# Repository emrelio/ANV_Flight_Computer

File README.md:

Flight computer design for experimental model rocket flights.

I design this PCB for TVC of low power rockets.

Specs:

3-12V battery input,
  
Reverse battery protection,
  
3.3V and 5V switching regulators,
  
One main arm switch connector to cut all the power from the board,
  
Magnetic Switch connector for activation,
  
4, high current logic outputs,
  
All high current outputs have feedback for continuity detection,
  
4, 5v Servo outputs,
  
1,  LED and 1, active Buzzer connector,
  
1, RGB LED for notification,
  
ARM MCU,
  
Battery voltage and current sensors,
  
2, barometer from different brands for reliability,
  
9 DOF IMU,
  
4MB of memory for data logging,
  
Type-C connector for reading logged data,
  
433mHz LoRa for long-range wireless communication with U.FL connection,
  
Notification LED's for memory write and wireless communication,
  
Notification LED's for each high current outputs,
  
Screw terminal connector for power in-outs,
  
CAN-Bus connector for expansions in future,
  
M3 screw holes are connected to (BATT+, BATT-(GND), CAN-H, CAN-L).

Designed in KiCAD nightly.

Log:
  
Hall effect sensor out pin needs pull-up resistor, not pull-down. So It doesn't work.  
3.3V regulator acting abnormally. I might overheated it while soldering. Will try it on another board.  
IMU and Barometers are working.  
USB VCP is working.  
Current sensor is working.  
Mosfet feedback is working.  
Flash memory is working, logging algorithm is ready.  
Servo is working with integrated 5V regulator. Voltage might drop on load.  
  
To-Do :

Lora  
Can-Bus

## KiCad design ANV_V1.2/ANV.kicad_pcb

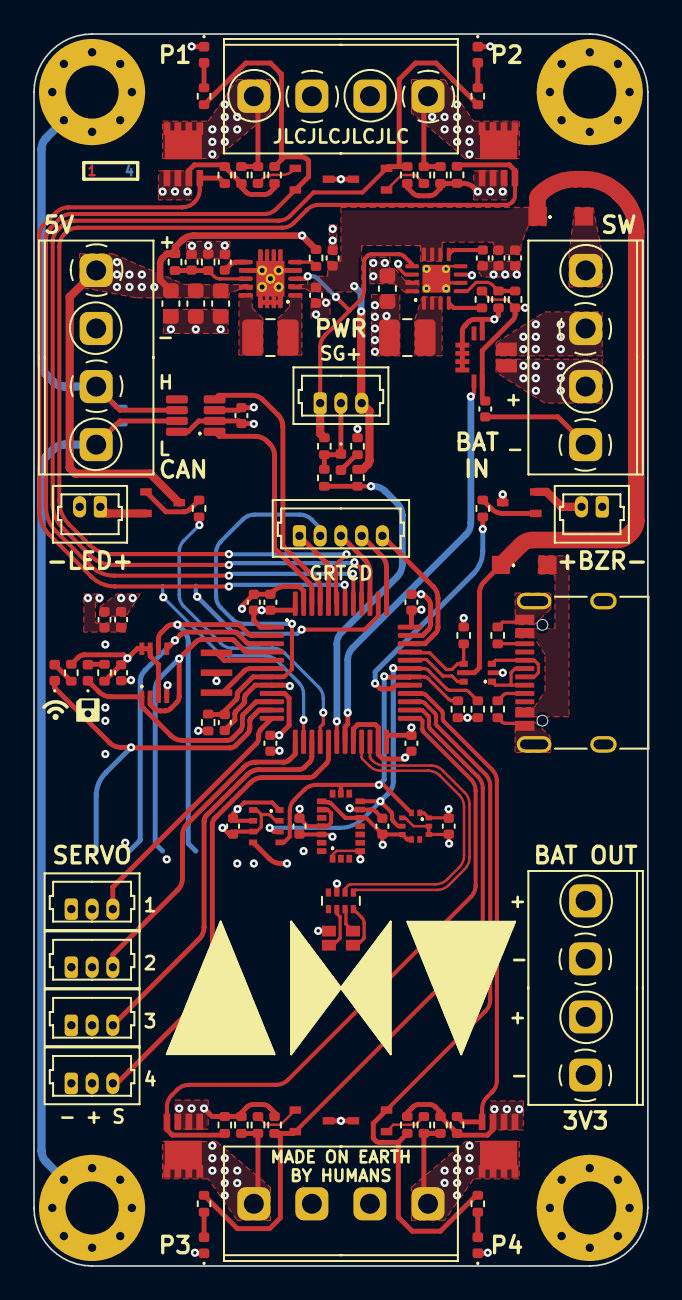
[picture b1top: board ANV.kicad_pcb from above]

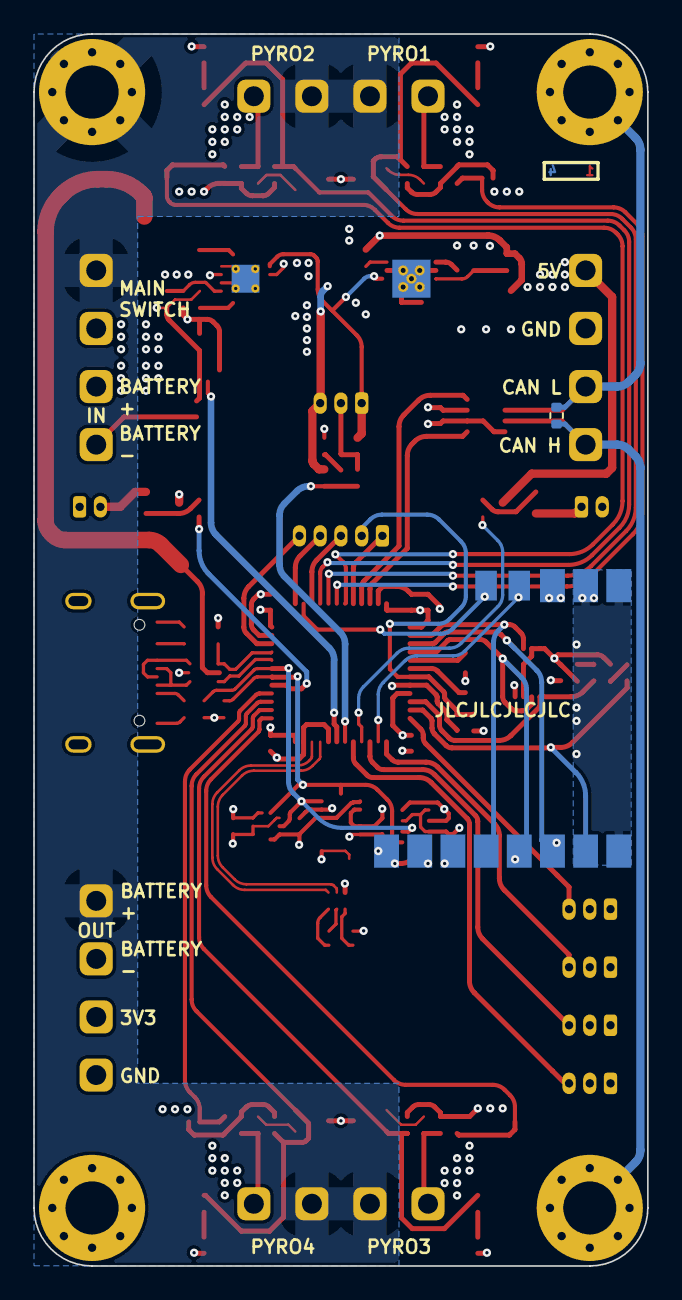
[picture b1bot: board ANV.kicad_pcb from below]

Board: 4 copper layers, 37.0 x 74.3 mm, 128 parts (2 on the bottom side), 83 nets.

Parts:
C1, C3, C7, C13, C14, C15, C16, C17, C18, C19, C20, C21, C23, C24, C25, C26, C27: 100nF; C_0402_1005Metric
C2, C4, C5: 10uF; C_0402_1005Metric
C6: 390pF; C_0402_1005Metric
C8: 10pF; C_0402_1005Metric
C9, C10, C11, C12: 22uF; C_0603_1608Metric
D1, D9: diode; D_SOD-123F
D2: flash; LED_0402_1005Metric
D3: pyro1; LED_0402_1005Metric
D4: pyro2; LED_0402_1005Metric
D5: pyro3; LED_0402_1005Metric
D6: pyro4; LED_0402_1005Metric
D7: 3v3; LED_0402_1005Metric
D8: RGB_Led; LED_LiteOn_LTST-C19HE1WT
D10: lora; LED_0402_1005Metric
H1: L; MountingHole_3.2mm_M3_Pad_Via
H2: H; MountingHole_3.2mm_M3_Pad_Via
H3: GND; MountingHole_3.2mm_M3_Pad_Via
H4: pwr; MountingHole_3.2mm_M3_Pad_Via
J1: programlama; Molex_PicoBlade_53047-0510_1x05_P1.25mm_Vertical
J2: Batt; 3.5mm_01x02_Screw_Terminal
J3: Sw; 3.5mm_01x02_Screw_Terminal
J4: USB_C_Receptacle_USB2.0; USB_C_Receptacle_XKB_U262-16XN-4BVC11
J5: switch/hallEffect; Molex_PicoBlade_53047-0310_1x03_P1.25mm_Vertical
J6: buzzer; Molex_PicoBlade_53047-0210_1x02_P1.25mm_Vertical
J7: 5v; 3.5mm_01x02_Screw_Terminal
J8: canbus; 3.5mm_01x02_Screw_Terminal
J9: led; Molex_PicoBlade_53047-0210_1x02_P1.25mm_Vertical
J10: pyro1; 3.5mm_01x02_Screw_Terminal
J11: pyro2; 3.5mm_01x02_Screw_Terminal
J12: pyro3; 3.5mm_01x02_Screw_Terminal
J13: pyro4; 3.5mm_01x02_Screw_Terminal
J14: servo1; Molex_PicoBlade_53047-0310_1x03_P1.25mm_Vertical
J15: servo2; Molex_PicoBlade_53047-0310_1x03_P1.25mm_Vertical
J16: batt; 3.5mm_01x02_Screw_Terminal
J17: 3v; 3.5mm_01x02_Screw_Terminal
J18: servo3; Molex_PicoBlade_53047-0310_1x03_P1.25mm_Vertical
J19: servo4; Molex_PicoBlade_53047-0310_1x03_P1.25mm_Vertical
L1: 1uH; L_1008_2520Metric
L2: 2.2uH; L_1008_2520Metric
LOGO1: anv; .A.N.V._Logo
LOGO2: rf; wifi
LOGO3: save; floppy
Q1, Q2, Q3, Q4: SE20N110; Vishay_PowerPAK_1212-8_Single
Q5, Q6, Q7, Q8, Q9, Q10: BC817W; SOT-323_SC-70
R1, R11: 100k; R_0402_1005Metric
R2: 30k; R_0402_1005Metric
R3, R4: 5k1; R_0402_1005Metric
R7, R12, R14, R15, R16, R17, R18, R19, R20, R21, R26, R27, R28, R29: 10k; R_0402_1005Metric
R8: 1k5; R_0402_1005Metric
R9, R39: 1m; R_0402_1005Metric
R10: 110k; R_0402_1005Metric
R13, R22, R23, R24, R25, R30, R31, R32, R33, R34, R35, R36, R45: 1k; R_0402_1005Metric
R37, R38: 4k7; R_0402_1005Metric
R40: 562k; R_0402_1005Metric
R41: 180k; R_0402_1005Metric
R44: 120r; R_0402_1005Metric
RN1: 1k; R_Array_Concave_4x0402
U1: ACS711xEXLT-15AB; Allegro_QFN-12-10-1EP_3x3mm_P0.5mm
U2: USBLC6-2P6; SOT-666
U3: TLV62130ARGTR; VQFN-16-1EP_3x3mm_P0.5mm_EP1.68x1.68mm_ThermalVias
U4: TPS63060; Texas_S-PWSON-N10_ThermalVias
U5: STM32F302C8Tx; LQFP-48_7x7mm_P0.5mm
U6: W25X40CLUXIG; DFN-8-1EP_3x2mm_P0.5mm_EP1.3x1.5mm
U7: LPS22HBTR; LPS22HB
U8: BMP280; Bosch_LGA-8_2x2.5mm_P0.65mm_ClockwisePinNumbering
U9: BMX055
U11: MAX3051; SOT-23-8
U12: Ai-Thinker-Ra-02; Ai-Thinker-Ra-01-LoRa
Y1: 8mHz; Resonator_SMD_muRata_CSTxExxV-3Pin_3.0x1.1mm

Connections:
+3V3: C1.1, C10.1, C14.2, C15.2, C16.2, C17.2, C18.2, C19.2, C20.1, C21.1, C23.2, C24.2, C25.2, C26.2, C27.2, D8.2 (VCC), J17.2, L2.2, Q5.3 (C), Q6.3 (C), Q9.3 (C), Q10.3 (C), R8.1, R11.1, R12.1, R13.1, R36.1, R37.1, R38.1, R40.1, R45.1, U1.10 (VCC), U3.7 (FSW), U3.14 (VOS), U5.1 (VBAT), U5.9 (VDDA), U5.24 (VDD), U5.36 (VDD), U5.48 (VDD), U6.3 (IO2), U6.7 (IO3), U6.8 (VCC), U7.1 (VDD_IO), U7.5 (SDO), U7.6 (CS), U7.10 (VDD), U8.2 (CSB), U8.6 (VDDIO), U8.8 (VDD), U9.3 (VDD), U9.7 (PS), U9.13 (VDDIO), U11.3 (VDD), U12.3 (VDD)
+5V: C9.1, C11.1, C12.1, J7.1, J14.2, J15.2, J18.2, J19.2, Q7.3 (C), Q8.3 (C), R9.1, R39.1, U4.9 (VOUT)
A0: D2.1 (K), U5.10 (PA0), U6.1 (~CS)
A1: D10.1 (K), U5.11 (PA1), U12.15 (~NSS)
A2: J14.3, U5.12 (PA2)
A3: J15.3, U5.13 (PA3)
A5: J18.3, U5.15 (PA5)
A6: R31.1, U5.16 (PA6)
A7: J19.3, U5.17 (PA7)
A8: R30.1, U5.29 (PA8)
A9: R37.2, U5.30 (PA9), U7.2 (SCL), U8.4 (SCK), U9.9 (SCX)
A10: R38.2, U5.31 (PA10), U7.4 (SDA), U8.3 (SDI), U9.11 (SDX)
A15: U5.38 (PA15), U12.5 (DIO0)
B0: R1.1, R2.2, U5.18 (PB0)
B1: U1.9 (VIOUT), U5.19 (PB1)
B3: J1.3, U5.39 (PB3)
B4: Q6.2 (E), R27.2, R33.1, U5.40 (PB4)
B5: Q5.2 (E), R26.2, R32.1, U5.41 (PB5)
B6: Q1.4 (G), R14.2, U5.42 (PB6)
B7: Q2.4 (G), R15.2, U5.43 (PB7)
B10: RN1.2 (R2.1), U5.21 (PB10)
B11: RN1.1 (R1.1), U5.22 (PB11)
B12: Q3.4 (G), R16.2, U5.25 (PB12)
B13: Q9.2 (E), R28.2, R34.1, U5.26 (PB13)
B14: Q10.2 (E), R29.2, R35.1, U5.27 (PB14)
B15: Q4.4 (G), R17.2, U5.28 (PB15)
Batt_+: C2.1, C3.1, C4.1, C5.1, D1.1 (K), D9.1 (K), J5.3, R1.2, U2.5 (VBUS), U3.10 (AVIN), U3.11 (PVIN), U3.12 (PVIN), U4.2 (VIN)
Batt_Pyro: D9.2 (A), H4.1, J3.2, J10.1, J11.2, J12.2, J13.1, J16.2
C13: U5.2 (PC13), U6.6 (CLK), U12.12 (SCK)
C14: U5.3 (PC14), U6.5 (DI(IO0)), U12.14 (MOSI)
C15: U5.4 (PC15), U6.2 (DO(IO1)), U12.13 (MISO)
GND: C1.2, C2.2, C3.2, C4.2, C5.2, C6.1, C7.2, C8.2, C9.2, C10.2, C11.2, C12.2, C13.1, C14.1, C15.1, C16.1, C17.1, C18.1, C19.1, C20.2, C21.2, C23.1, C24.1, C25.1, C26.1, C27.1, D3.1 (K), D4.1 (K), D5.1 (K), D6.1 (K), D7.1 (K), H3.1, J1.1, J2.1, J4.A1 (GND), J4.A12 (GND), J4.B1 (GND), J4.B12 (GND), J4.S1 (SHIELD), J5.2, J6.1, J7.2, J9.2, J14.1, J15.1, J16.1, J17.1, J18.1, J19.1, Q1.1 (S), Q1.2 (S), Q1.3 (S), Q2.1 (S), Q2.2 (S), Q2.3 (S), Q3.1 (S), Q3.2 (S), Q3.3 (S), Q4.1 (S), Q4.2 (S), Q4.3 (S), R2.1, R3.2, R4.2, R7.1, R10.2, R14.1, R15.1, R16.1, R17.1, R18.1, R19.1, R20.1, R21.1, R26.1, R27.1, R28.1, R29.1, R41.2, RN1.3 (R3.1), U1.3 (GND), U1.5 (NC), U1.6 (NC), U1.7 (NC), U1.8 (NC), U2.2 (GND), U3.6 (AGND), U3.8 (DEF), U3.15 (PGND), U3.16 (PGND), U3.17 (THERMAL_PAD), U4.4 (PS/SYNC), U4.7 (GND), U4.11 (PGND), U5.8 (VSSA), U5.20 (PB2), U5.23 (VSS), U5.35 (VSS), U5.44 (BOOT0), U5.47 (VSS), U6.4 (GND), U7.3 (-), U7.8 (GND), U7.9 (GND), U8.1 (GND), U8.5 (SDO), U8.7 (GND), U9.4 (GNDA), U9.6 (GNDIO), U9.12 (SDO2), U9.17 (SDO1), U9.20 (CSB3(magnet)), U11.2 (GND), U11.8 (RS), U12.1 (GND), U12.2 (GND), U12.9 (GND), U12.16 (GND), Y1.2
unnamed: C6.2, U3.9 (SS/TR)
unnamed: C7.1, U4.6 (VAUX)
unnamed: C8.1, R9.2, R10.1, U4.8 (FB)
unnamed: D1.2 (A), J4.A4 (VBUS), J4.A9 (VBUS), J4.B4 (VBUS), J4.B9 (VBUS)
unnamed: D2.2 (A), R13.2
unnamed: D3.2 (A), R32.2
unnamed: D4.2 (A), R33.2
unnamed: D5.2 (A), R34.2
unnamed: D6.2 (A), R35.2
unnamed: D7.2 (A), R36.2
unnamed: D8.1 (B), RN1.6 (R3.2)
unnamed: D8.3 (G), RN1.7 (R2.2)
unnamed: D8.4 (R), RN1.8 (R1.2)
unnamed: D10.2 (A), R45.2
unnamed: J2.2, U1.1 (IP+)
unnamed: J3.1, U1.2 (IP-)
unnamed: J4.A5 (CC1), R3.1
unnamed: J4.A6 (D+), J4.B6 (D+), U2.3 (I/O2)
unnamed: J4.A7 (D-), J4.B7 (D-), U2.1 (I/O1)
unnamed: J4.B5 (CC2), R4.1
unnamed: L1.1, U4.1 (L1)
unnamed: L1.2, U4.10 (L2)
unnamed: L2.1, U3.1 (SW), U3.2 (SW), U3.3 (SW)
unnamed: Q5.1 (B), R22.2
unnamed: Q6.1 (B), R23.2
unnamed: Q7.1 (B), R30.2
unnamed: Q8.1 (B), R31.2
unnamed: Q9.1 (B), R24.2
unnamed: Q10.1 (B), R25.2
unnamed: R11.2, U3.4 (PG)
unnamed: R39.2, U4.5 (PG)
unnamed: R40.2, R41.1, U3.5 (FB)
unnamed: U5.5 (PF0), Y1.1
unnamed: U5.6 (PF1), Y1.3
Reset: C13.2, J1.2, R12.2, U5.7 (NRST)
SWCLK: J1.4, U5.37 (PA14)
SWDIO: J1.5, U5.34 (PA13)
USB_D+: R8.2, U2.4 (I/O2), U5.33 (PA12)
USB_D-: U2.6 (I/O1), U5.32 (PA11)
buzzer_out: J6.2, Q7.2 (E)
can_H: H2.1, J8.2, R44.1, U11.7 (CANH)
can_L: H1.1, J8.1, R44.2, U11.6 (CANL)
canrx: U5.45 (PB8), U11.4 (RXD)
cantx: U5.46 (PB9), U11.1 (TXD)
en: J5.1, R7.2, U3.13 (EN), U4.3 (EN)
led_out: J9.1, Q8.2 (E)
lora_reset: U5.14 (PA4), U12.4 (~RESET)
pyro1_out: J10.2, Q1.5 (D), R18.2, R22.1
pyro2_out: J11.1, Q2.5 (D), R19.2, R23.1
pyro3_out: J12.1, Q3.5 (D), R20.2, R24.1
pyro4_out: J13.2, Q4.5 (D), R21.2, R25.1
